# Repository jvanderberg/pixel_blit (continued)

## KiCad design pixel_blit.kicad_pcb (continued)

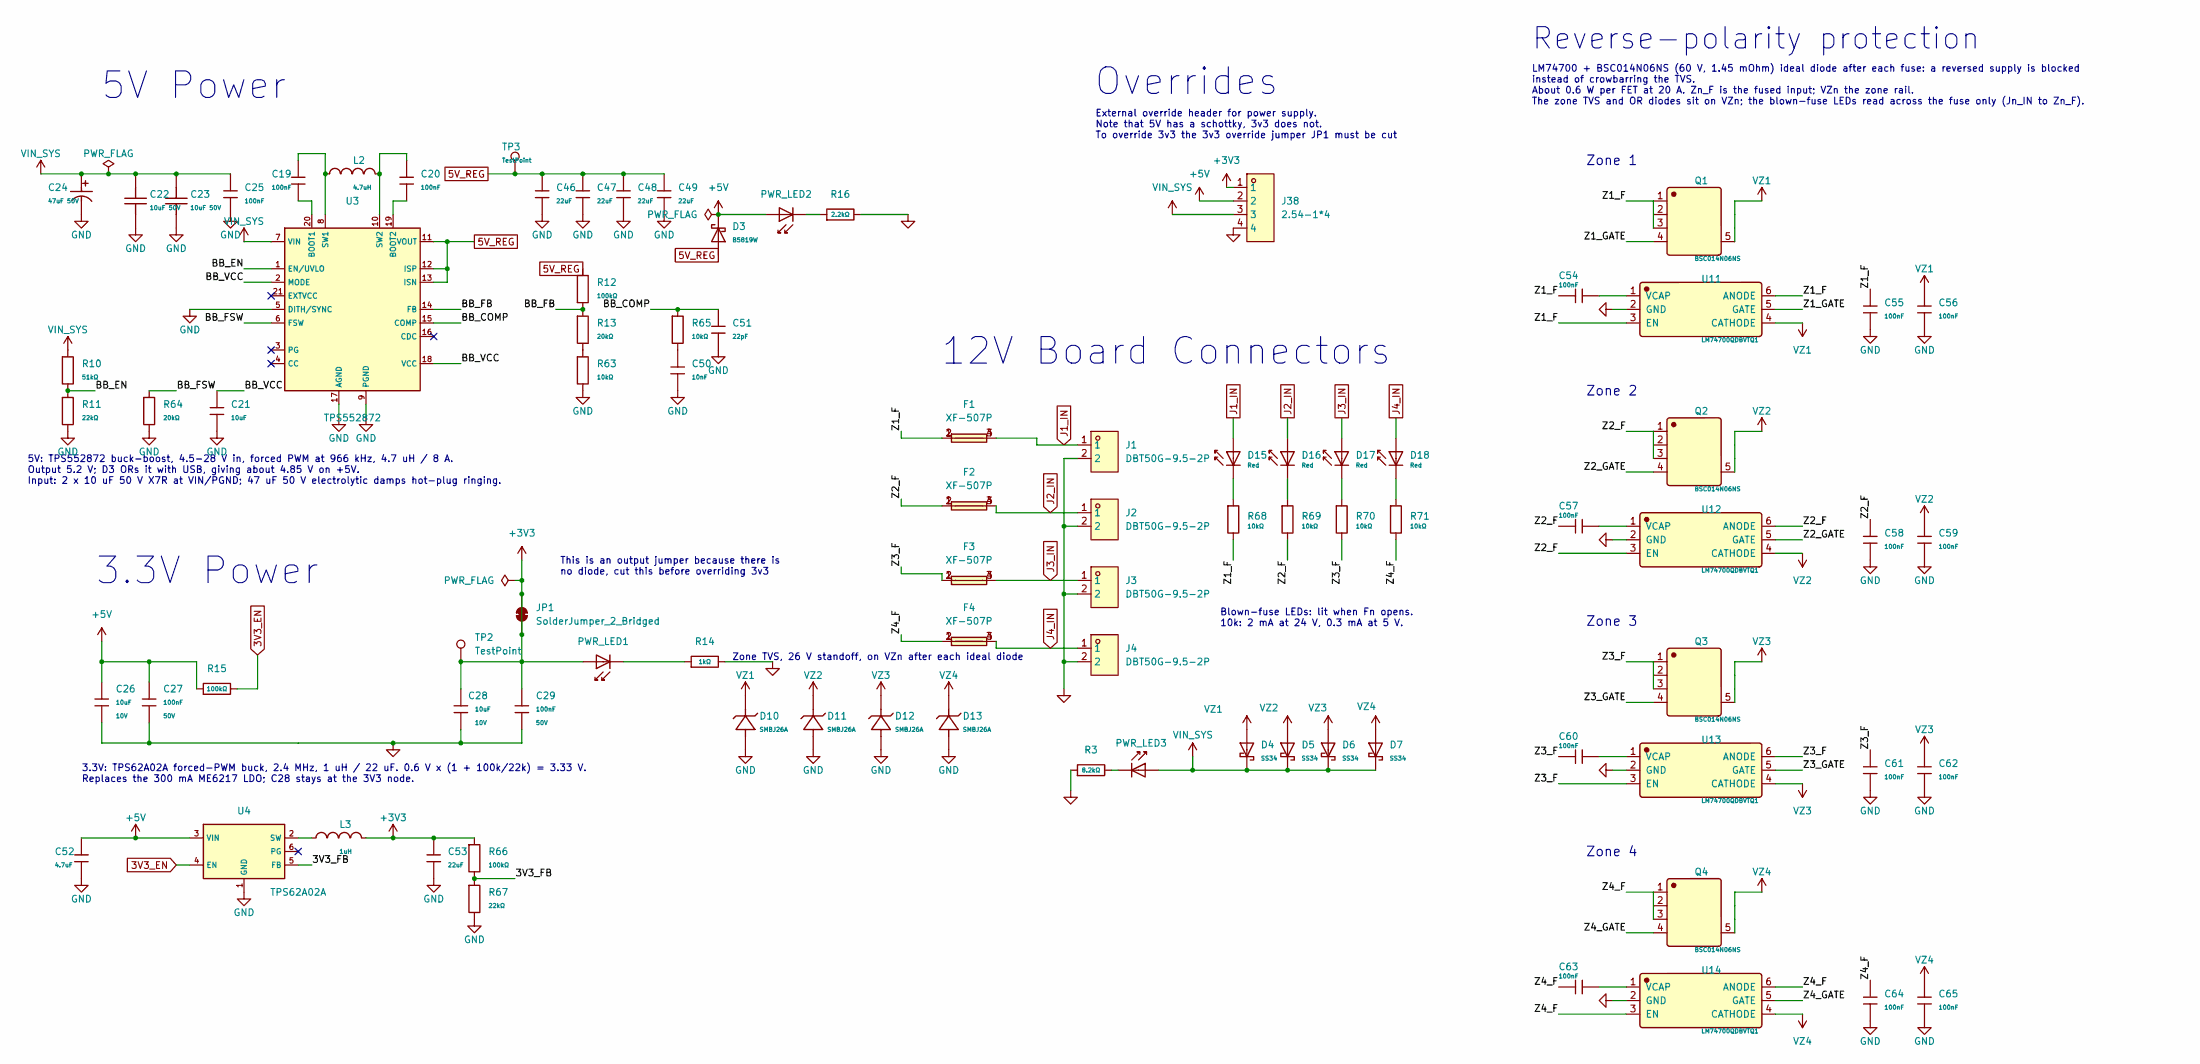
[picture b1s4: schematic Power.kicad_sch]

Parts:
C19, C20: 100nF; C_0402; Voltage Rated 16V; Tolerance ±10%; Part CL05B104KO5NNNC; LCSC C1525
C21, C26, C28: 10uF; C_0603; Voltage Rated 10V; Tolerance ±10%; Part CL10A106KP8NNNC; LCSC C19702
C22, C23: 10uF 50V; CL31B106KBHNNNE; Manufacturer Part CL31B106KBHNNNE; LCSC C89632
C24: 47uF 50V; RVT1H470M0607; Manufacturer Part RVT1H470M0607; LCSC C72523
C25, C27, C29, C54, C55, C56, C57, C58, C59, C60, C61, C62, C63, C64, C65: 100nF; C_0603; Voltage Rated 50V; Tolerance ±10%; Part CC0603KRX7R9BB104; LCSC C14663
C46, C47, C48, C49, C53: 22uF; C_0805; Voltage Rated 25V; Tolerance ±20%; Part CL21A226MAQNNNE; LCSC C45783
C50: 10nF; C_0402; Voltage Rated 50V; Tolerance ±10%; Part CL05B103KB5NNNC; LCSC C15195
C51: 22pF; C_0402; Voltage Rated 50V; Tolerance ±5%; Part 0402CG220J500NT; LCSC C1555
C52: 4.7uF; C_0603; Voltage Rated 16V; Tolerance ±10%; Part CL10A475KO8NNNC; LCSC C19666
D3: B5819W; D_SOD-123; Forward Voltage (Vf@If) 900mV@3A; Reverse Voltage (Vr) 40V; Part B5819W; LCSC C64885
D4, D5, D6, D7: SS34; D_SMA; Forward Voltage (Vf@If) 550mV@3A; Reverse Voltage (Vr) 40V; Part SS34; LCSC C8678
D10, D11, D12, D13: SMBJ26A; SMBJ26A_C726831; Manufacturer Part SMBJ26A; LCSC C726831
D15, D16, D17, D18: Red; D_0603; Part KT-0603R; LCSC C2286
F1, F2, F3, F4: XF-507P; Manufacturer Part XF-507P; LCSC C668119
J1, J2, J3, J4: DBT50G-9.5-2P; CONN-TH_2P-P9.50_DBT50G-9.5-2P; LCSC Part C395958
J38: 2.54-1*4; HDR-TH_4P-P2.54-V-M-1; LCSC Part C5116483
JP1: SolderJumper_2_Bridged
L2: 4.7uH; MWSA0605S-4R7MT; Manufacturer Part MWSA0605S-4R7MT; LCSC C408465
L3: 1uH; DFE201612E-1R0M_P2; Manufacturer Part DFE201612E-1R0M=P2; LCSC C337892
PWR_LED1, PWR_LED2, PWR_LED3: Red; D_0603; Part KT-0603R; LCSC C2286
Q1, Q2, Q3, Q4: BSC014N06NS; Manufacturer Part BSC014N06NS; LCSC C113391
R3: 8.2kΩ; R_0603; Overload Voltage (Max) 75V; Tolerance ±1%; Part 0603WAF8201T5E; LCSC C25981
R10: 51kΩ; R_0402; Overload Voltage (Max) 50V; Tolerance ±1%; Part 0402WGF5102TCE; LCSC C25794
R11, R67: 22kΩ; R_0402; Overload Voltage (Max) 50V; Tolerance ±1%; Part 0402WGF2202TCE; LCSC C25768
R12, R15, R66: 100kΩ; R_0402; Overload Voltage (Max) 50V; Tolerance ±1%; Part 0402WGF1003TCE; LCSC C25741
R13, R64: 20kΩ; R_0402; Overload Voltage (Max) 50V; Tolerance ±1%; Part 0402WGF2002TCE; LCSC C25765
R14: 1kΩ; R_0402; Overload Voltage (Max) 50V; Tolerance ±1%; Part 0402WGF1001TCE; LCSC C11702
R16: 2.2kΩ; R_0603; Overload Voltage (Max) 75V; Tolerance ±1%; Part 0603WAF2201T5E; LCSC C4190
R63, R65: 10kΩ; R_0402; Overload Voltage (Max) 50V; Tolerance ±1%; Part 0402WGF1002TCE; LCSC C25744
R68, R69, R70, R71: 10kΩ; R_0603; Overload Voltage (Max) 75V; Tolerance ±1%; Part 0603WAF1002T5E; LCSC C25804
TP2, TP3: TestPoint; TestPoint_Pad_1.0x1.0mm
U3: TPS552872; TPS552872QWRYQRQ1; Part TPS552872QWRYQRQ1; LCSC C22397842
U4: TPS62A02A; TPS62A02ADRLR; Part TPS62A02ADRLR; LCSC C5820994
U11, U12, U13, U14: LM74700QDBVTQ1; Manufacturer Part LM74700QDBVTQ1; LCSC C2653623

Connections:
3V3_EN: R15.2, U4.4 (EN)
5V_REG: C46.1, C47.1, C48.1, C49.1, D3.2, R12.1, TP3.1, U3.11 (VOUT), U3.12 (ISP), U3.13 (ISN)
+3V3: C28.1, C29.1, C53.1, J38.1, JP1.1 (A), JP1.2 (B), L3.2, PWR_LED1.2, R66.1, TP2.1; also elsewhere on the board
+5V: C26.1, C27.1, C52.1, D3.1, J38.2, PWR_LED2.2, R15.1, U4.3 (VIN); also elsewhere on the board
/Power/3V3_FB: R66.2, R67.1, U4.5 (FB)
/Power/BB_COMP: C51.1, R65.1, U3.15 (COMP)
/Power/BB_EN: R10.2, R11.1, U3.1 (EN/UVLO)
/Power/BB_FB: R12.2, R13.1, U3.14 (FB)
/Power/BB_FSW: R64.1, U3.6 (FSW)
/Power/BB_VCC: C21.1, U3.2 (MODE), U3.18 (VCC)
/Power/Z1_F: C54.1, C55.1, F1.1, F1.2, Q1.1 (S), Q1.2 (S), Q1.3 (S), R68.2, U11.3 (EN), U11.6 (ANODE)
/Power/Z1_GATE: Q1.4 (G), U11.5 (GATE)
/Power/Z2_F: C57.1, C58.1, F2.1, F2.2, Q2.1 (S), Q2.2 (S), Q2.3 (S), R69.2, U12.3 (EN), U12.6 (ANODE)
/Power/Z2_GATE: Q2.4 (G), U12.5 (GATE)
/Power/Z3_F: C60.1, C61.1, F3.1, F3.2, Q3.1 (S), Q3.2 (S), Q3.3 (S), R70.2, U13.3 (EN), U13.6 (ANODE)
/Power/Z3_GATE: Q3.4 (G), U13.5 (GATE)
/Power/Z4_F: C63.1, C64.1, F4.1, F4.2, Q4.1 (S), Q4.2 (S), Q4.3 (S), R71.2, U14.3 (EN), U14.6 (ANODE)
/Power/Z4_GATE: Q4.4 (G), U14.5 (GATE)
GND: C21.2, C22.1, C23.1, C24.2, C25.2, C26.2, C27.2, C28.2, C29.2, C46.2, C47.2, C48.2, C49.2, C50.2, C51.2, C52.2, C53.2, C55.2, C56.2, C58.2, C59.2, C61.2, C62.2, C64.2, C65.2, D10.2 (A), D11.2 (A), D12.2 (A), D13.2 (A), J1.2, J2.2, J3.2, J4.2, J38.4, R3.1, R11.2, R14.2, R16.2, R63.2, R64.2, R67.2, U3.5 (DITH/SYNC), U3.9 (PGND), U3.17 (AGND), U4.1 (GND), U11.2 (GND), U12.2 (GND), U13.2 (GND), U14.2 (GND); also elsewhere on the board
J1_IN: D15.2, F1.3, F1.4, J1.1
J2_IN: D16.2, F2.3, F2.4, J2.1
J3_IN: D17.2, F3.3, F3.4, J3.1
J4_IN: D18.2, F4.3, F4.4, J4.1
unnamed: C50.1, R65.2
unnamed: D15.1, R68.1
unnamed: D16.1, R69.1
unnamed: D17.1, R70.1
unnamed: D18.1, R71.1
unnamed: PWR_LED1.1, R14.1
unnamed: PWR_LED2.1, R16.1
unnamed: PWR_LED3.1, R3.2
unnamed: R13.2, R63.1
unnamed: C19.2, U3.20 (BOOT1)
unnamed: C20.2, U3.19 (BOOT2)
unnamed: C19.1, L2.1, U3.8 (SW1)
unnamed: C20.1, L2.2, U3.10 (SW2)
unnamed: L3.1, U4.2 (SW)
unnamed: C54.2, U11.1 (VCAP)
unnamed: C57.2, U12.1 (VCAP)
unnamed: C60.2, U13.1 (VCAP)
unnamed: C63.2, U14.1 (VCAP)
VIN_SYS: C22.2, C23.2, C24.1, C25.1, D4.1, D5.1, D6.1, D7.1, J38.3, PWR_LED3.2, R10.1, U3.7 (VIN)
VZ1: C56.1, D4.2, D10.1 (C), Q1.5 (D), U11.4 (CATHODE); also elsewhere on the board
VZ2: C59.1, D5.2, D11.1 (C), Q2.5 (D), U12.4 (CATHODE); also elsewhere on the board
VZ3: C62.1, D6.2, D12.1 (C), Q3.5 (D), U13.4 (CATHODE); also elsewhere on the board
VZ4: C65.1, D7.2, D13.1 (C), Q4.5 (D), U14.4 (CATHODE); also elsewhere on the board

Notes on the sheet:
External override header for power supply. Note that 5V has a schottky, 3v3 does not. To override 3v3 the 3v3 override jumper JP1 must be cut
Zone TVS, 26 V standoff, on VZn after each ideal diode
3.3V Power
3.3V: TPS62A02A forced-PWM buck, 2.4 MHz, 1 uH / 22 uF. 0.6 V x (1 + 100k/22k) = 3.33 V. Replaces the 300 mA ME6217 LDO; C28 stays at the 3V3 node.
Overrides
This is an output jumper because there is no diode, cut this before overriding 3v3
5V: TPS552872 buck-boost, 4.5-28 V in, forced PWM at 966 kHz, 4.7 uH / 8 A. Output 5.2 V; D3 ORs it with USB, giving about 4.85 V on +5V. Input: 2 x 10 uF 50 V X7R at VIN/PGND; 47 uF 50 V electrolytic damps hot-plug ringing.
Blown-fuse LEDs: lit when Fn opens. 10k: 2 mA at 24 V, 0.3 mA at 5 V.
12V Board Connectors
5V Power
Reverse-polarity protection
LM74700 + BSC014N06NS (60 V, 1.45 mOhm) ideal diode after each fuse: a reversed supply is blocked instead of crowbarring the TVS. About 0.6 W per FET at 20 A. Zn_F is the fused input; VZn the zone rail. The zone TVS and OR diodes sit on VZn; the blown-fuse LEDs read across the fuse only (Jn_IN to Z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
Zone 1
Zone 2
Zone 3
Zone 4

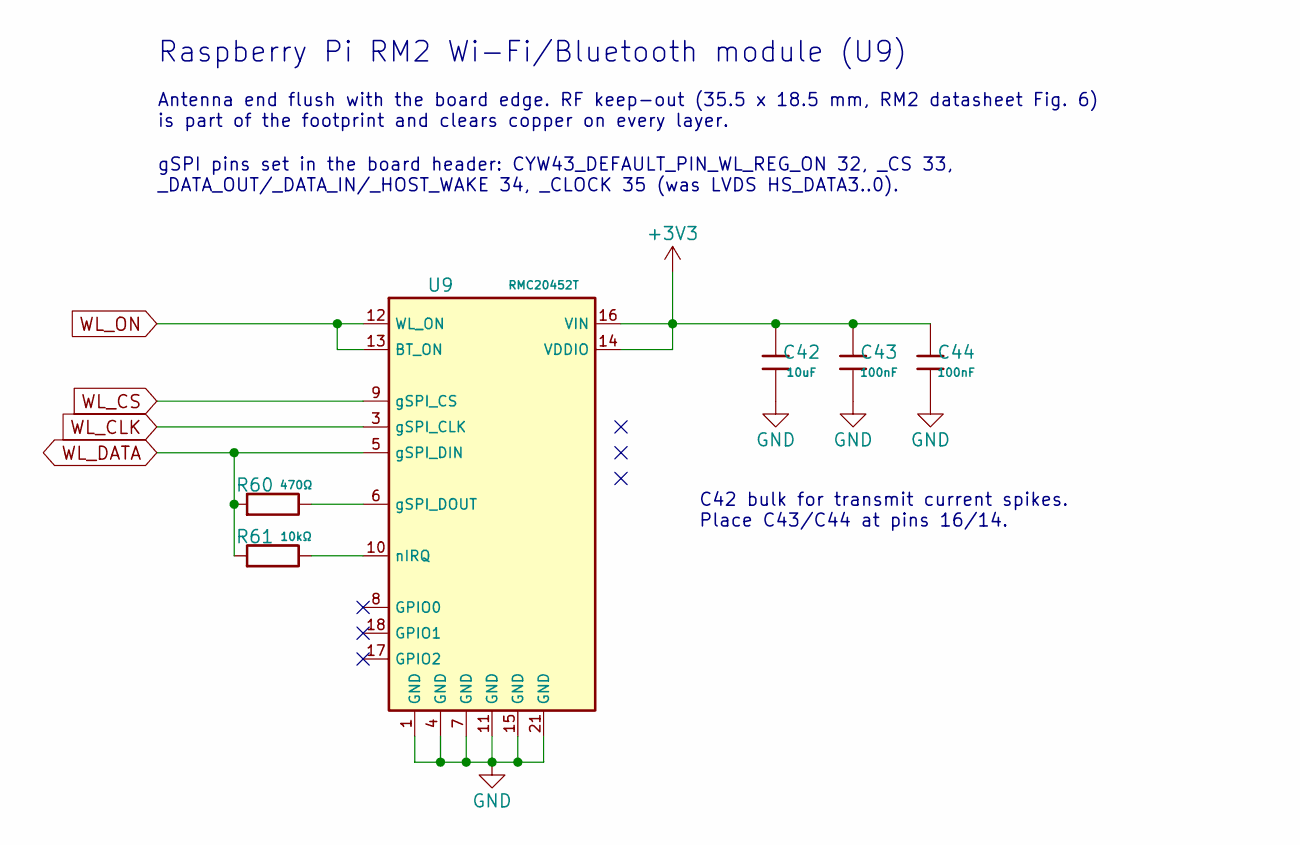
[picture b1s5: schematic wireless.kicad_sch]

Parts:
C42: 10uF; C_0603; Voltage Rated 10V; Tolerance ±10%; Part CL10A106KP8NNNC; LCSC C19702
C43, C44: 100nF; C_0402; Voltage Rated 16V; Tolerance ±10%; Part CL05B104KO5NNNC; LCSC C1525
R60: 470Ω; R_0402; Overload Voltage (Max) 50V; Tolerance ±1%; Part 0402WGF4700TCE; LCSC C25117
R61: 10kΩ; R_0402; Overload Voltage (Max) 50V; Tolerance ±1%; Part 0402WGF1002TCE; LCSC C25744
U9: RMC20452T; RMC20452T_C49451547; Part RMC20452T; LCSC C49451547

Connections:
+3V3: C42.1, C43.1, C44.1, U9.14 (VDDIO), U9.16 (VIN); also elsewhere on the board
GND: C42.2, C43.2, C44.2, U9.1 (GND), U9.4 (GND), U9.7 (GND), U9.11 (GND), U9.15 (GND), U9.21 (GND); also elsewhere on the board
unnamed: R60.2, U9.6 (gSPI_DOUT)
unnamed: R61.2, U9.10 (nIRQ)
WL_CLK: U9.3 (gSPI_CLK); also elsewhere on the board
WL_CS: U9.9 (gSPI_CS); also elsewhere on the board
WL_DATA: R60.1, R61.1, U9.5 (gSPI_DIN); also elsewhere on the board
WL_ON: U9.12 (WL_ON), U9.13 (BT_ON); also elsewhere on the board

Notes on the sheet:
gSPI pins set in the board header: CYW43_DEFAULT_PIN_WL_REG_ON 32, _CS 33, _DATA_OUT/_DATA_IN/_HOST_WAKE 34, _CLOCK 35 (was LVDS HS_DATA3..0).
C42 bulk for transmit current spikes. Place C43/C44 at pins 16/14.
Antenna end flush with the board edge. RF keep-out (35.5 x 18.5 mm, RM2 datasheet Fig. 6) is part of the footprint and clears copper on every layer.
Raspberry Pi RM2 Wi-Fi/Bluetooth module (U9)

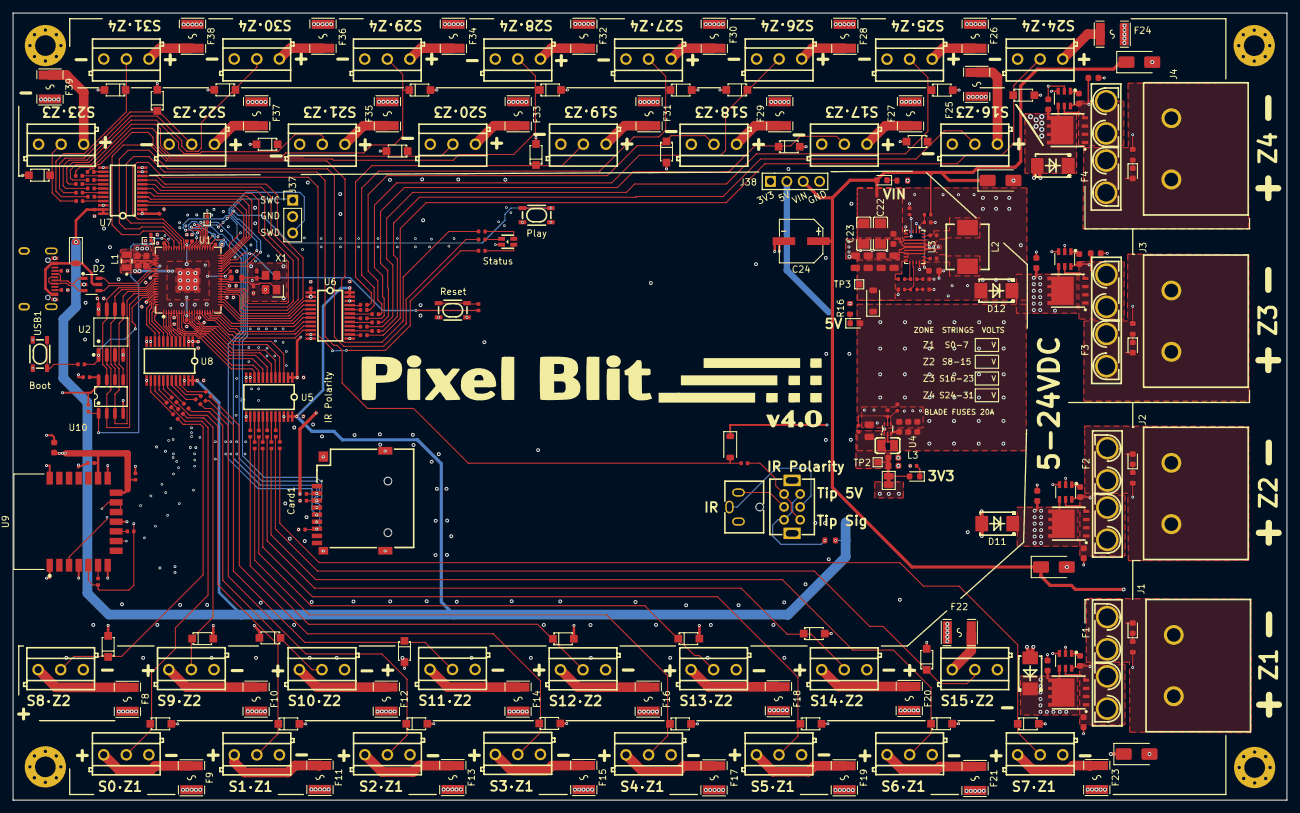
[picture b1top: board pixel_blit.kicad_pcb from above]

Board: 4 copper layers, 197.5 x 122.0 mm, 291 parts (0 on the bottom side), 222 nets.

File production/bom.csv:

Designator,Footprint,Quantity,Value,LCSC Part #
"C1, C10, C11, C12, C13, C2, C25, C3, C30, C31, C32, C33, C34, C35, C36, C37, C38, C4, C40, C5, C6, C7, C8, C9",C_0402,24,100nF,C1525
C14,C_0402,1,4.7uF,C23733
"C15, C16",C_0603,2,4.7uF,C19666
"C17, C18",C0402,2,15pF,C1548
"C19, C24",C_0603,2,10uF,C96446
C20,C_0805,1,10uF,C440198
C21,C_0805,1,47uF,C16780
"C22, C23",C_0805,2,22uF,C45783
"C26, C28",C_0603,2,10uF,C19702
"C27, C29",C_0603,2,100nF,C14663
"C39, C41",C_0402,2,1nF,C1523
CARD1,TF-SMD_TF-PUSH,1,TF PUSH,C393941
CN1,AUDIO-TH_XKB_PJ-3059-B,1,PJ-3059-B,C2884976
"D1, D3",D_SOD-123,2,B5819W,C64885
D10,SOD-123_L2.7-W1.6-LS3.7-RD-1,1,BZT52C15V,C5182294
D2,SOT-23-6_L2.9-W1.6-P0.95-LS2.8-BL,1,USBLC6-2SC6,C7519
"D4, D5, D6, D7",D_SMA,4,SS34,C8678
"F1, F2, F3, F4, F5, F6, F7",FUSE-TH_4P-L19.8-W6.7_3557-2,7,3557-2,C352820
"F10, F11, F12, F13, F14, F15, F16, F17, F18, F19, F20, F21, F22, F23, F24, F25, F26, F27, F28, F29, F30, F31, F32, F33, F34, F35, F36, F37, F38, F39, F8, F9",F1812,32,1812L400/16GR,C22374900
"J1, J2, J3, J4",CONN-TH_2P-P9.50_DBT50G-9.5-2P,4,DBT50G-9.5-2P,C395958
"J10, J11, J12, J13, J14, J15, J16, J17, J18, J19, J20, J21, J22, J23, J24, J25, J26, J27, J28, J29, J30, J31, J32, J33, J34, J35, J36, J5, J6, J7, J8, J9",CONN-TH_DB301V-3.5-3P-GN,32,DB301V-3.5-3P-GN,C695630
J37,PinHeader_1x03_P2.54mm_Vertical,1,Conn_01x03_Pin,
J38,HDR-TH_4P-P2.54-V-M-1,1,2.54-1*4,C5116483
J39,HDR-TH_9P-P2.54-V-M,1,PZ2.54-1*9,C5360901
L1,IND-SMD_L2.0-W1.6_AOTA-B201610S3R3-101-T,1,~,C42411119
L2,IND-SMD_L4.4-W4.2,1,FXL0420-1R5-M,C167205
"PWR_LED1, PWR_LED2, PWR_LED3",D_0603,3,Red,C2286
"R1, R14, R18",R_0402,3,1kΩ,C11702
R10,R_0603,1,10kΩ,C25804
"R11, R13",R_0603,2,100kΩ,C25803
R12,R0402,1,560kΩ,C132339
R15,R_0402,1,100kΩ,C25741
R16,R_0603,1,2.2kΩ,C4190
"R19, R24, R25, R26, R27, R28, R29, R30, R31, R32, R33, R34, R35, R36, R37, R38, R39, R40, R41, R42, R43, R44, R45, R46, R47, R48, R49, R50, R51, R52, R53, R54",R_0402,32,47Ω,C25118
R2,R_0603,1,100Ω,C22775
"R20, R21, R22, R23",R_0402,4,100Ω,C25076
R3,R_0603,1,8.2kΩ,C25981
"R57, R58, R59",R_0402,3,47kΩ,C25792
R6,R0402,1,33Ω,C25105
"R7, R8",R_0402,2,5.1kΩ,C25905
R9,R_0603,1,1kΩ,C21190
RESET1,KEY-SMD_4P-L4.2-W3.2-P2.20-LS5.1-TL,1,K2-1808SN-A4SW-01,C92589
"RJ1, RJ2",RJ45-TH_R-RJ45R08P-A004,2,R-RJ45R08P-A004,C385834
SW1,KEY-SMD_4P-L4.2-W3.2-P2.20-LS5.1-TL,1,K2-1808SN-A4SW,C92589
SW2,SW-TH_SS-22D03-G4,1,SS-22D03-G040,C2848923
"TP1, TP2, TP3",TestPoint_Pad_1.0x1.0mm,3,TestPoint,
U1,QFN-80_L10.0-W10.0-P0.40-TL-EP3.4,1,RP2350B_C42415655,C42415655
U2,SOIC-8_L5.3-W5.3-P1.27-LS8.0-BL,1,W25Q128JVSIQTR,C97521
U3,VQFN-HR-15_L3.0-W2.5-P0.50-BL_TPS63070RNMR,1,TPS63070RNMR,C109322
U4,SOT-23-5_L3.0-W1.7-P0.95-LS2.8-BR,1,~,C427602
U41,TSSOP-16_L5.0-W4.4-P0.65-LS6.4-BL,1,DSLVDS1048PWR,C2671655
U42,TSSOP-16_L5.0-W4.4-P0.65-LS6.4-TL,1,DSLVDS1047PWR,C2671205
"U5, U6, U7, U8",TSSOP-24_L7.8-W4.4-P0.65-LS6.4-BL,4,SN74LVC8T245PWR,C27643
USB1,USB-C-SMD_TYPE-C-6PIN-2MD-073,1,TYPE-C 16PIN 2MD(073),C2765186
X1,CRYSTAL-SMD_4P-L3.2-W2.5-BL,1,~,C20625731

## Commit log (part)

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2025-09-02 Created
2025-09-14 Checkpoint
2025-09-24 Close to final, lots of cleanup, added back audio
2025-09-24 Correct issue with gitignore
2025-11-04 Beef up power plane
2025-11-04 Readme
2025-11-05 Library shuffle and Fabrication Toolkit micro adjustments
2025-12-14 Add Polyform Noncommercial 1.0.0 license
2026-01-23 Working on errata
2026-01-25 Fixes for second production run
